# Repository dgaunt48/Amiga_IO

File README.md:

# MouseTest

RP2350 Program To Display Movement Counters,
Direction And Button Status Of An Amiga Mechanical Mouse.

# KeyboardTest

RP2350 Program To Decode And Display The Output From An A500 Keyboard.

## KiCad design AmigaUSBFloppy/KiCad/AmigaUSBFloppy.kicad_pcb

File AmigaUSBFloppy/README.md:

# Amiga USB Floppy

My Take On An Amiga GoTek Drive Using Parts I Had Lying Around.  Just A 2 Layer $2 PCB From JLC.

Firmware is at https://github.com/keirf/FlashFloppy

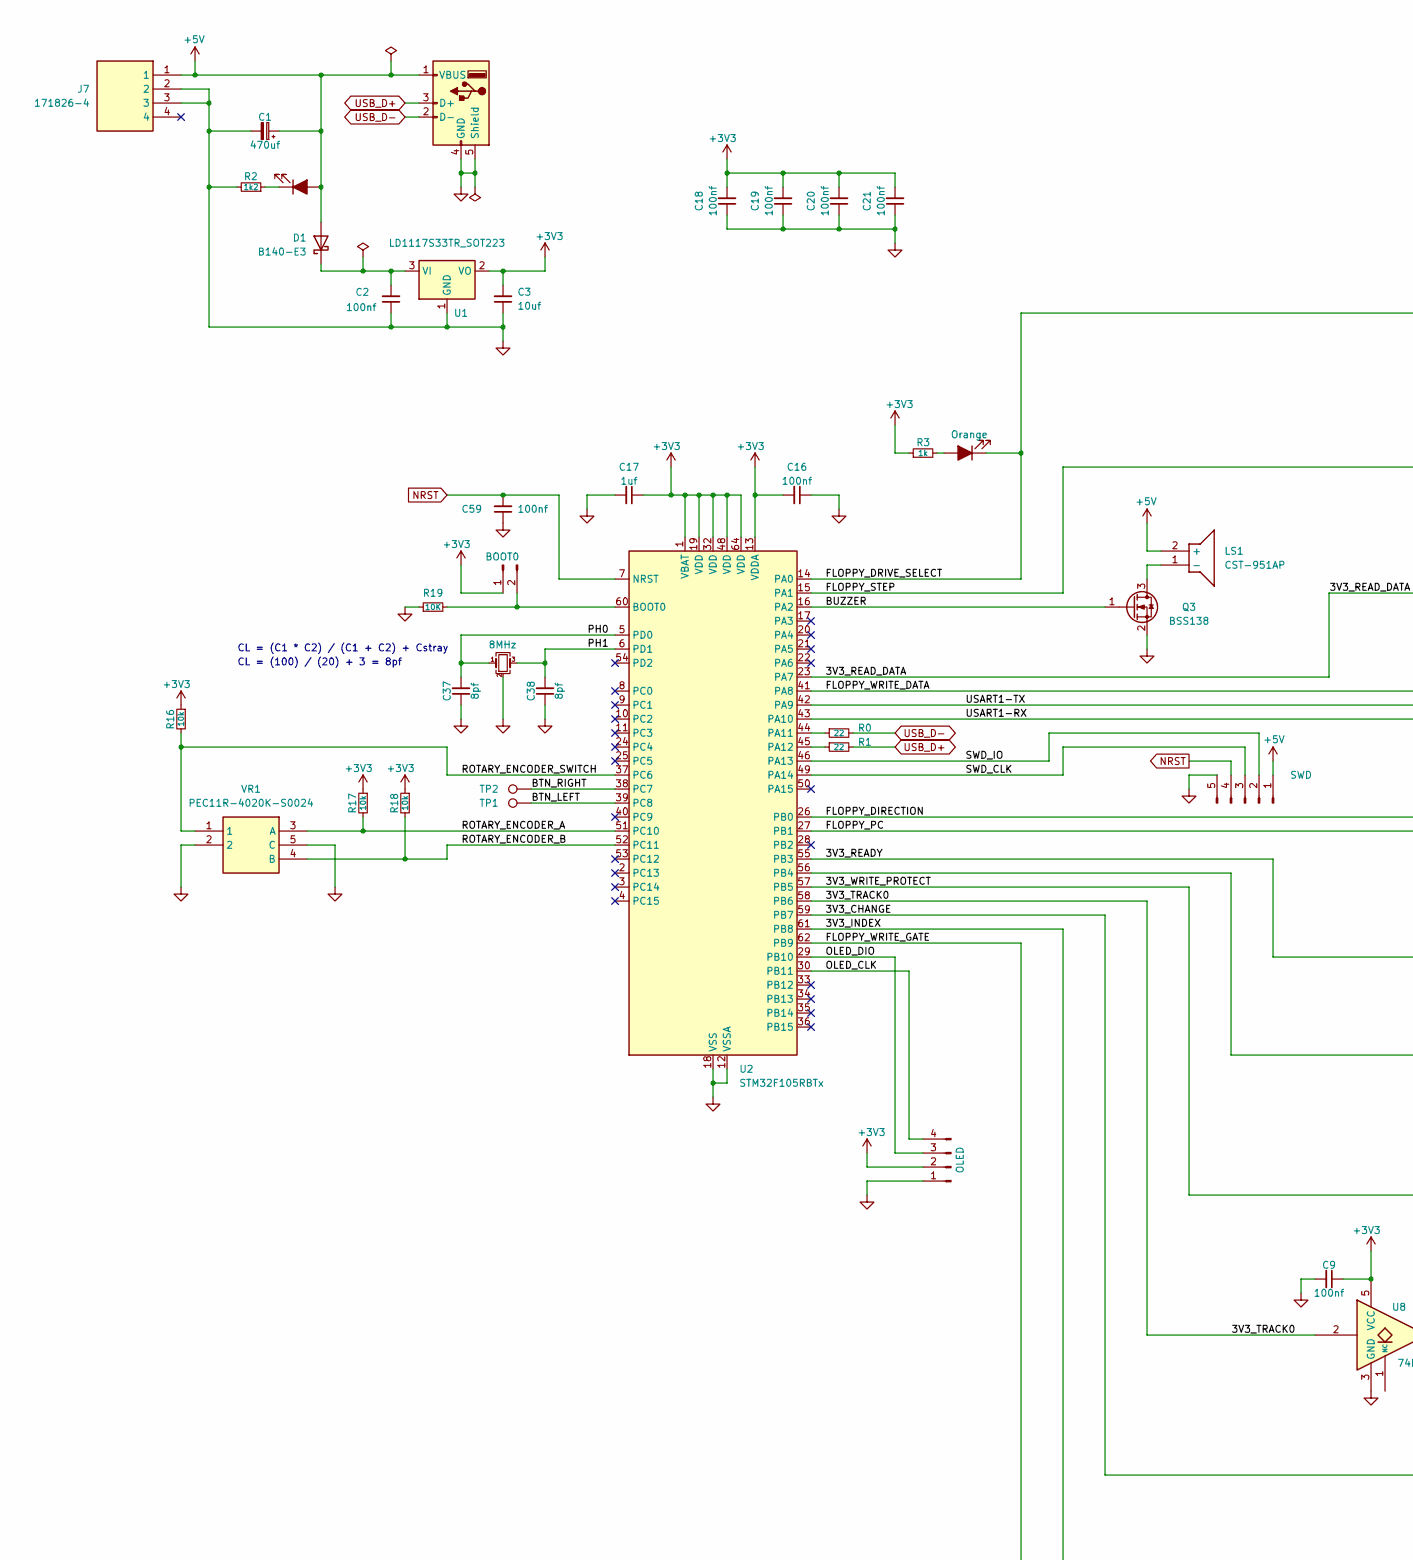
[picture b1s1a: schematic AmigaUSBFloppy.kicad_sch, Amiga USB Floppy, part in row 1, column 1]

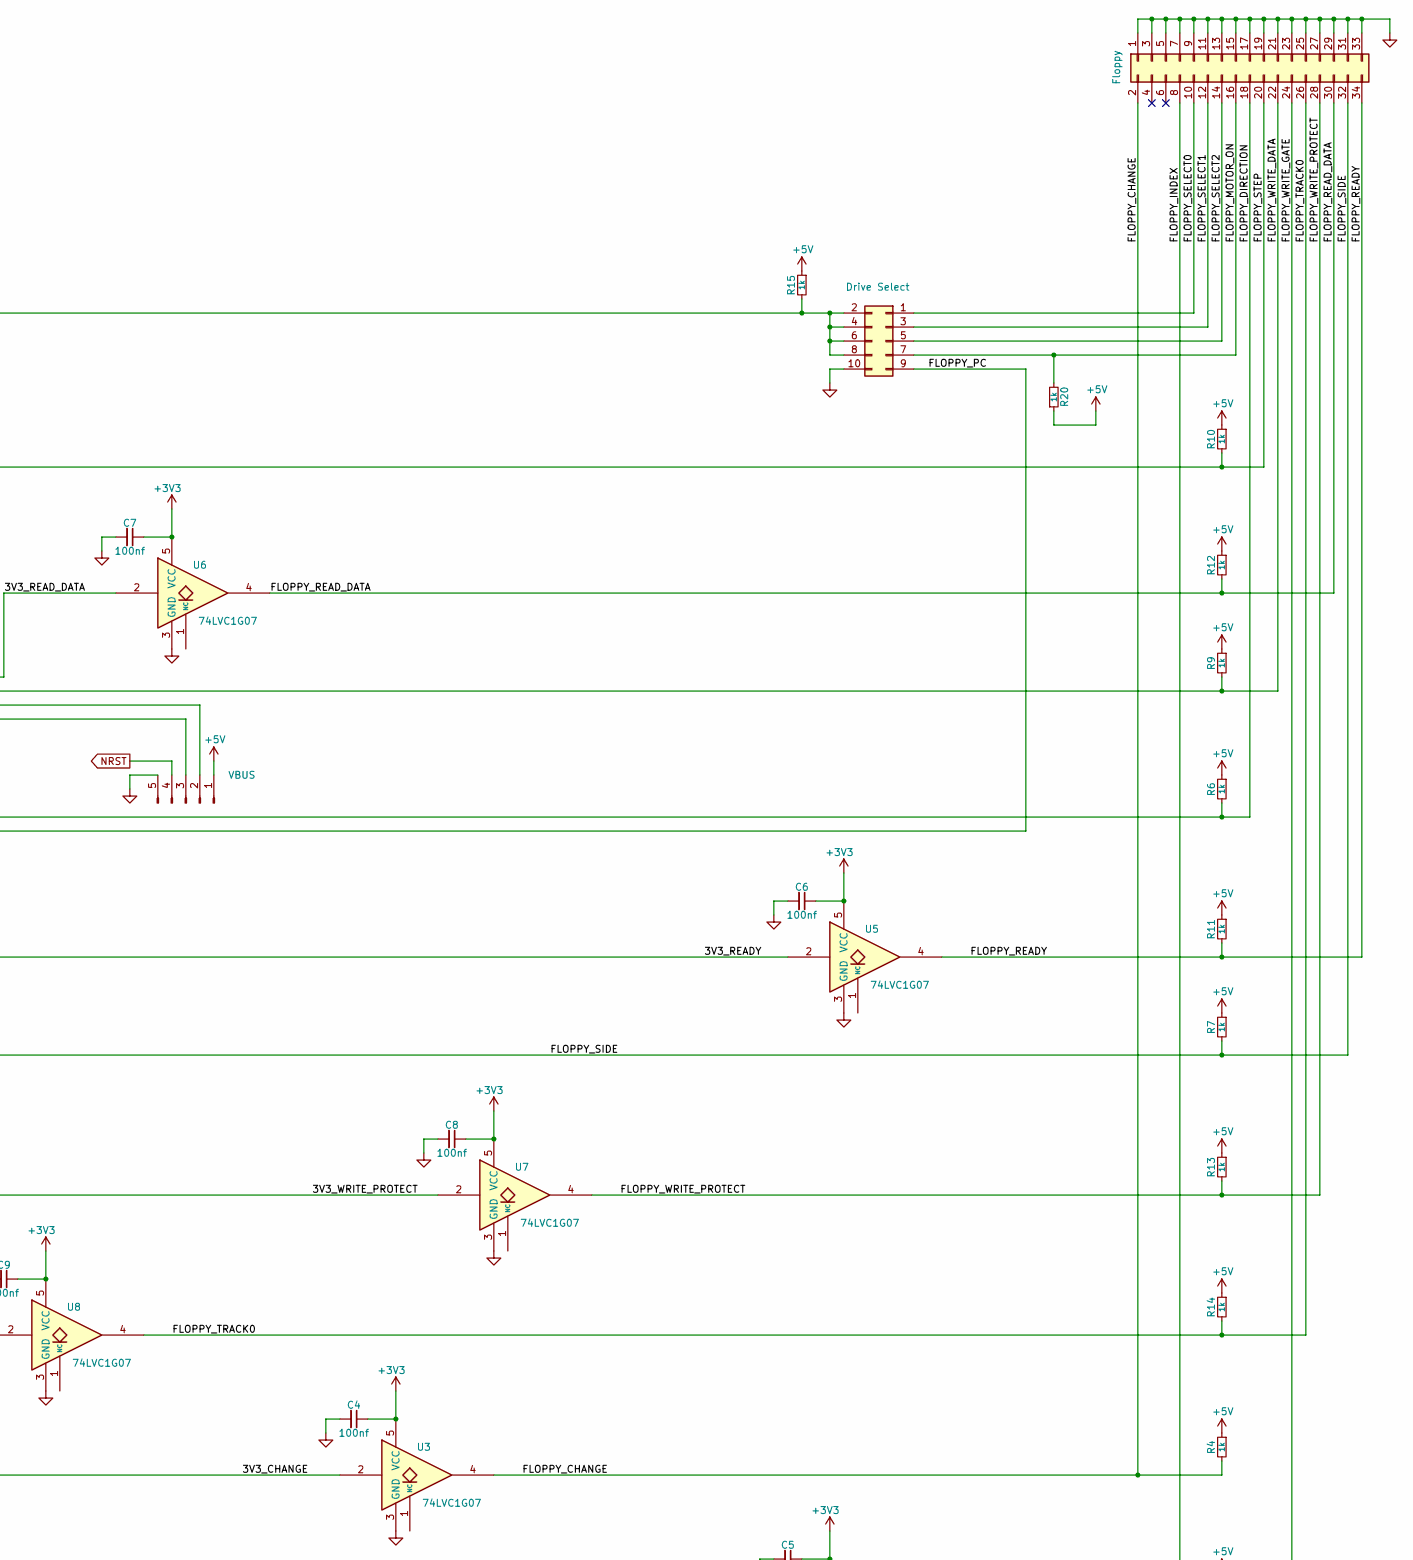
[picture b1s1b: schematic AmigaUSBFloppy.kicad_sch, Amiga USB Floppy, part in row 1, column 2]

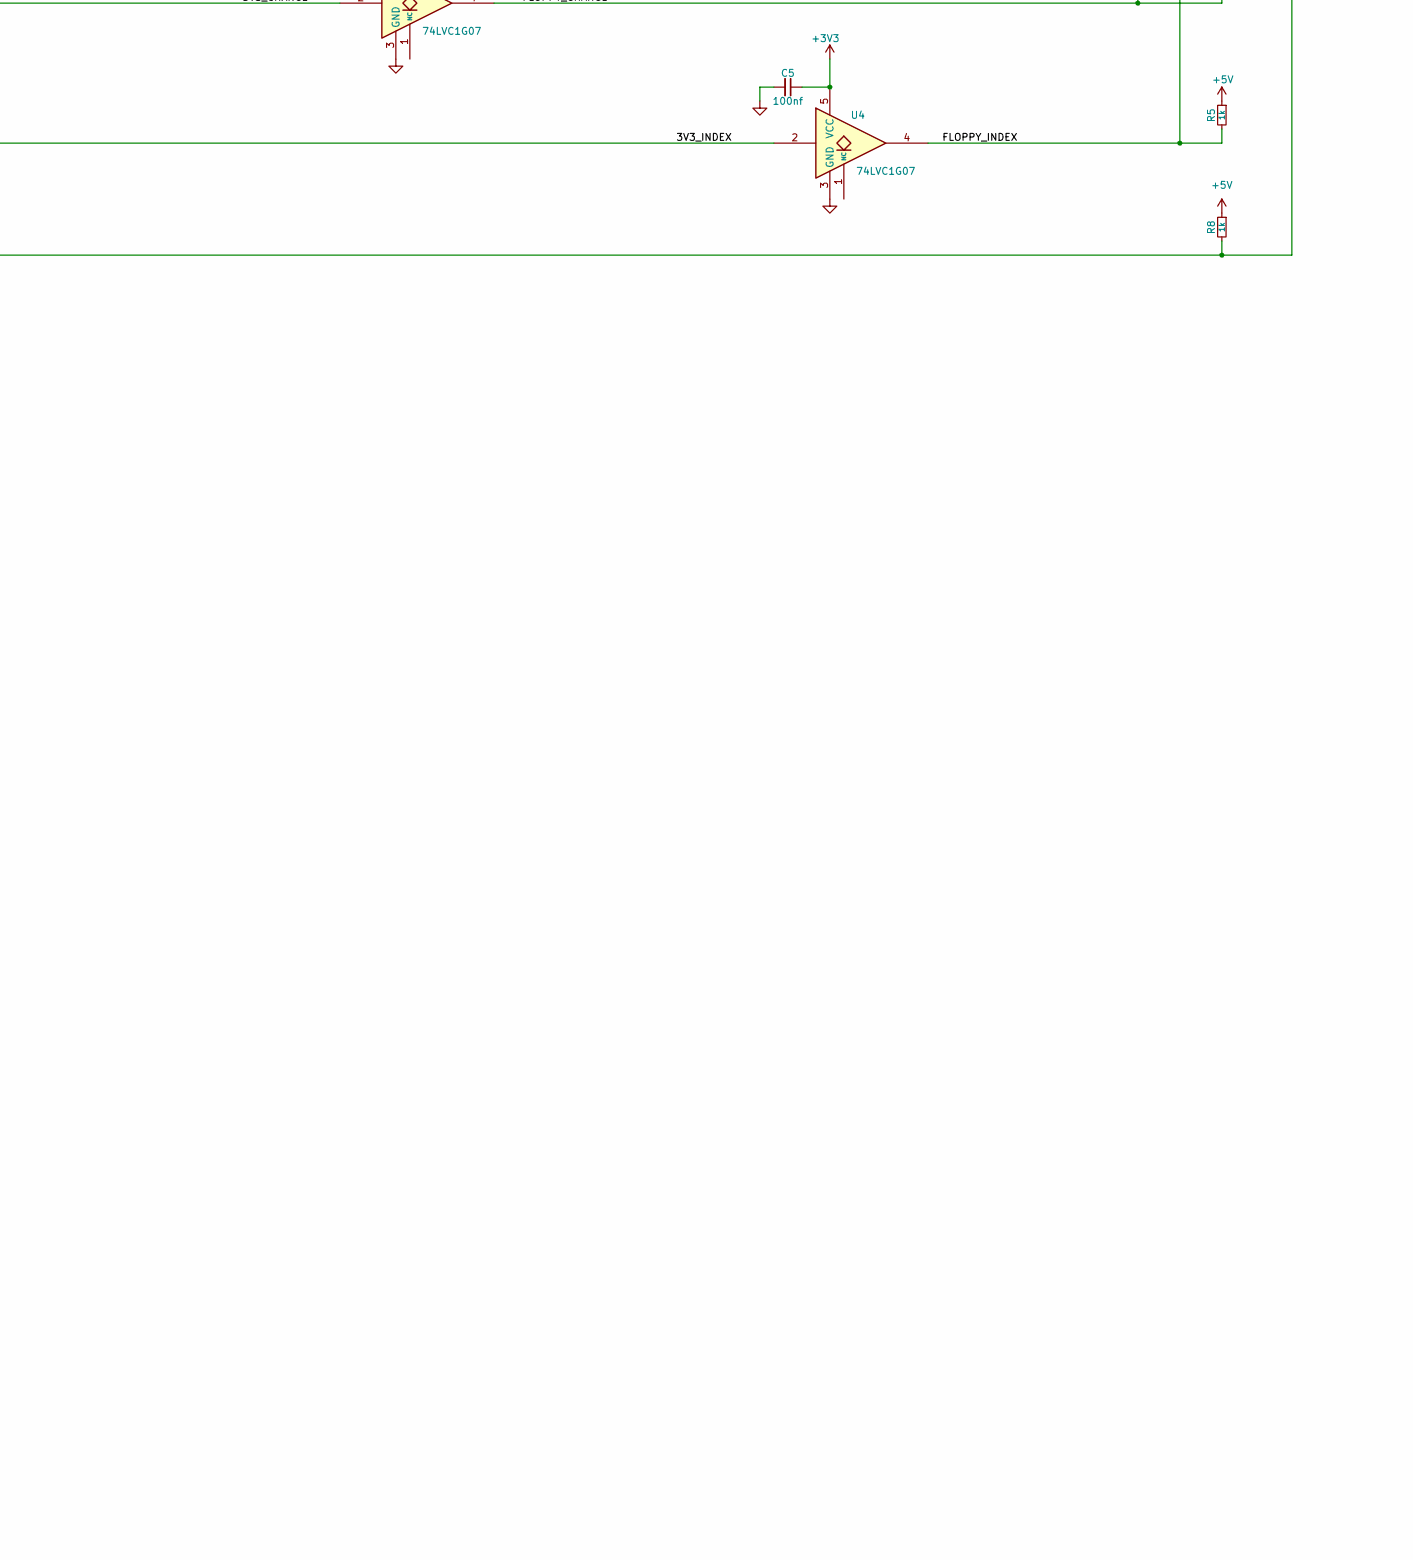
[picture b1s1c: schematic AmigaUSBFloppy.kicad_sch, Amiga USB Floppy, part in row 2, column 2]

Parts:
C1: 470uf; CP_Radial_D5.0mm_P2.50mm
C2, C4, C5, C6, C7, C8, C9, C16, C18, C19, C20, C21, C59: 100nf; C_0603_1608Metric
C3: 10uf; C_0805_2012Metric
C17: 1uf; C_0603_1608Metric
C37, C38: 8pf; C_0603_1608Metric
D1: B140-E3; D_SOD-123
H1, H2, H3, H4: MountingHole; MountingHole_2.5mm
J2: OLED; 128x64OLED
J3: Floppy; IDC-Header_2x17_P2.54mm_Vertical
J4: Drive Select; PinHeader_2x05_P2.54mm_Vertical
J5: BOOT0; PinHeader_1x02_P2.54mm_Vertical
J6: VBUS; PinHeader_1x05_P2.54mm_Vertical
J7: 171826-4; SHDRRA4W69P0X250_1X4_1000X1350X670P; Mouser Part Number 571-1718264
J11: SWD; PinHeader_1x05_P2.54mm_Vertical
J12: USB_A; USB_A_Molex_67643_Horizontal
LED1: POWER; LEDC2012X90N
LED2: Orange; LEDC2012X90N
LS1: CST-951AP; CST951AP; Mouser Part Number 490-CST-951AP
Q3: BSS138; SOT-23
R0, R1: 22; R_0603_1608Metric
R2: 1k2; R_0603_1608Metric
R3, R4, R5, R6, R7, R8, R9, R10, R11, R12, R13, R14, R15, R20: 1k; R_0603_1608Metric
R16, R17, R18: 10k; R_0603_1608Metric
R19: 10K; R_0603_1608Metric
TP1, TP2: TestPoint; TestPoint_Pad_1.0x1.0mm
U1: LD1117S33TR_SOT223; SOT-223-3_TabPin2; Voltage 3v3
U2: STM32F105RBTx; LQFP-64_10x10mm_P0.5mm
U3, U4, U5, U6, U7, U8: 74LVC1G07; SOT-353_SC-70-5
VR1: PEC11R-4020K-S0024; PEC11R-4XXXK-SXXXX; Mouser Part Number 652-PEC11R-4020K-S24
Y2: 8MHz; Crystal_SMD_SeikoEpson_FA238V-4Pin_3.2x2.5mm

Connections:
+3V3: C3.2, C4.1, C5.1, C6.1, C7.1, C8.1, C9.1, C16.2, C17.1, C18.2, C19.2, C20.2, C21.2, J2.2, J5.1, R3.1, R16.1, R17.1, R18.1, U1.2 (VO), U2.1 (VBAT), U2.13 (VDDA), U2.19 (VDD), U2.32 (VDD), U2.48 (VDD), U2.64 (VDD), U3.5 (VCC), U4.5 (VCC), U5.5 (VCC), U6.5 (VCC), U7.5 (VCC), U8.5 (VCC)
+5V: C1.1, D1.2 (A), J6.1, J7.1, J11.1, J12.1 (VBUS), LED1.2 (A), LS1.2 (+), R4.1, R5.1, R6.1, R7.1, R8.1, R9.1, R10.1, R11.1, R12.1, R13.1, R14.1, R15.1, R20.1
/3V3_CHANGE: U2.59 (PB7), U3.2
/3V3_INDEX: U2.61 (PB8), U4.2
/3V3_READY: U2.55 (PB3), U5.2
/3V3_READ_DATA: U2.23 (PA7), U6.2
/3V3_TRACK0: U2.58 (PB6), U8.2
/3V3_WRITE_PROTECT: U2.57 (PB5), U7.2
/BTN_LEFT: TP1.1, U2.39 (PC8)
/BTN_RIGHT: TP2.1, U2.38 (PC7)
/BUZZER: Q3.1 (G), U2.16 (PA2)
/FLOPPY_CHANGE: J3.2, R4.2, U3.4
/FLOPPY_DIRECTION: J3.18, R6.2, U2.26 (PB0)
/FLOPPY_DRIVE_SELECT: J4.2, J4.4, J4.6, J4.8, LED2.1 (K), R15.2, U2.14 (PA0)
/FLOPPY_INDEX: J3.8, R5.2, U4.4
/FLOPPY_MOTOR_ON: J3.16, J4.7, R20.2
/FLOPPY_PC: J4.9, U2.27 (PB1)
/FLOPPY_READY: J3.34, R11.2, U5.4
/FLOPPY_READ_DATA: J3.30, R12.2, U6.4
/FLOPPY_SELECT0: J3.10, J4.1
/FLOPPY_SELECT1: J3.12, J4.3
/FLOPPY_SELECT2: J3.14, J4.5
/FLOPPY_SIDE: J3.32, R7.2, U2.56 (PB4)
/FLOPPY_STEP: J3.20, R10.2, U2.15 (PA1)
/FLOPPY_TRACK0: J3.26, R14.2, U8.4
/FLOPPY_WRITE_DATA: J3.22, R9.2, U2.41 (PA8)
/FLOPPY_WRITE_GATE: J3.24, R8.2, U2.62 (PB9)
/FLOPPY_WRITE_PROTECT: J3.28, R13.2, U7.4
/OLED_CLK: J2.4, U2.30 (PB11)
/OLED_DIO: J2.3, U2.29 (PB10)
/PH0: C37.2, U2.5 (PD0), Y2.1
/PH1: C38.2, U2.6 (PD1), Y2.3
/ROTARY_ENCODER_A: R17.2, U2.51 (PC10), VR1.3 (A)
/ROTARY_ENCODER_B: R18.2, U2.52 (PC11), VR1.4 (B)
/ROTARY_ENCODER_SWITCH: R16.2, U2.37 (PC6), VR1.1
/SWD_CLK: J11.3, U2.49 (PA14)
/SWD_IO: J11.2, U2.46 (PA13)
/USART1-RX: J6.3, U2.43 (PA10)
/USART1-TX: J6.2, U2.42 (PA9)
GND: C1.2, C2.1, C3.1, C4.2, C5.2, C6.2, C7.2, C8.2, C9.2, C16.1, C17.2, C18.1, C19.1, C20.1, C21.1, C37.1, C38.1, C59.1, J2.1, J3.1, J3.3, J3.5, J3.7, J3.9, J3.11, J3.13, J3.15, J3.17, J3.19, J3.21, J3.23, J3.25, J3.27, J3.29, J3.31, J3.33, J4.10, J6.5, J7.2, J7.3, J11.5, J12.4 (GND), J12.5 (Shield), Q3.2 (S), R2.2, R19.1, U1.1 (GND), U2.12 (VSSA), U2.18 (VSS), U2.31 (VSS), U2.47 (VSS), U2.63 (VSS), U3.3 (GND), U4.3 (GND), U5.3 (GND), U6.3 (GND), U7.3 (GND), U8.3 (GND), VR1.2, VR1.5 (C), Y2.2 (G), Y2.4 (G)
NRST: C59.2, J6.4, J11.4, U2.7 (NRST)
unnamed: C2.2, D1.1 (K), U1.3 (VI)
unnamed: J5.2, R19.2, U2.60 (BOOT0)
unnamed: LED1.1 (K), R2.1
unnamed: LED2.2 (A), R3.2
unnamed: LS1.1 (-), Q3.3 (D)
unnamed: R0.1, U2.44 (PA11)
unnamed: R1.1, U2.45 (PA12)
USB_D+: J12.3 (D+), R1.2
USB_D-: J12.2 (D-), R0.2

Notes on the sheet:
CL = (100) / (20) + 3 = 8pf
CL = (C1 * C2) / (C1 + C2) + Cstray

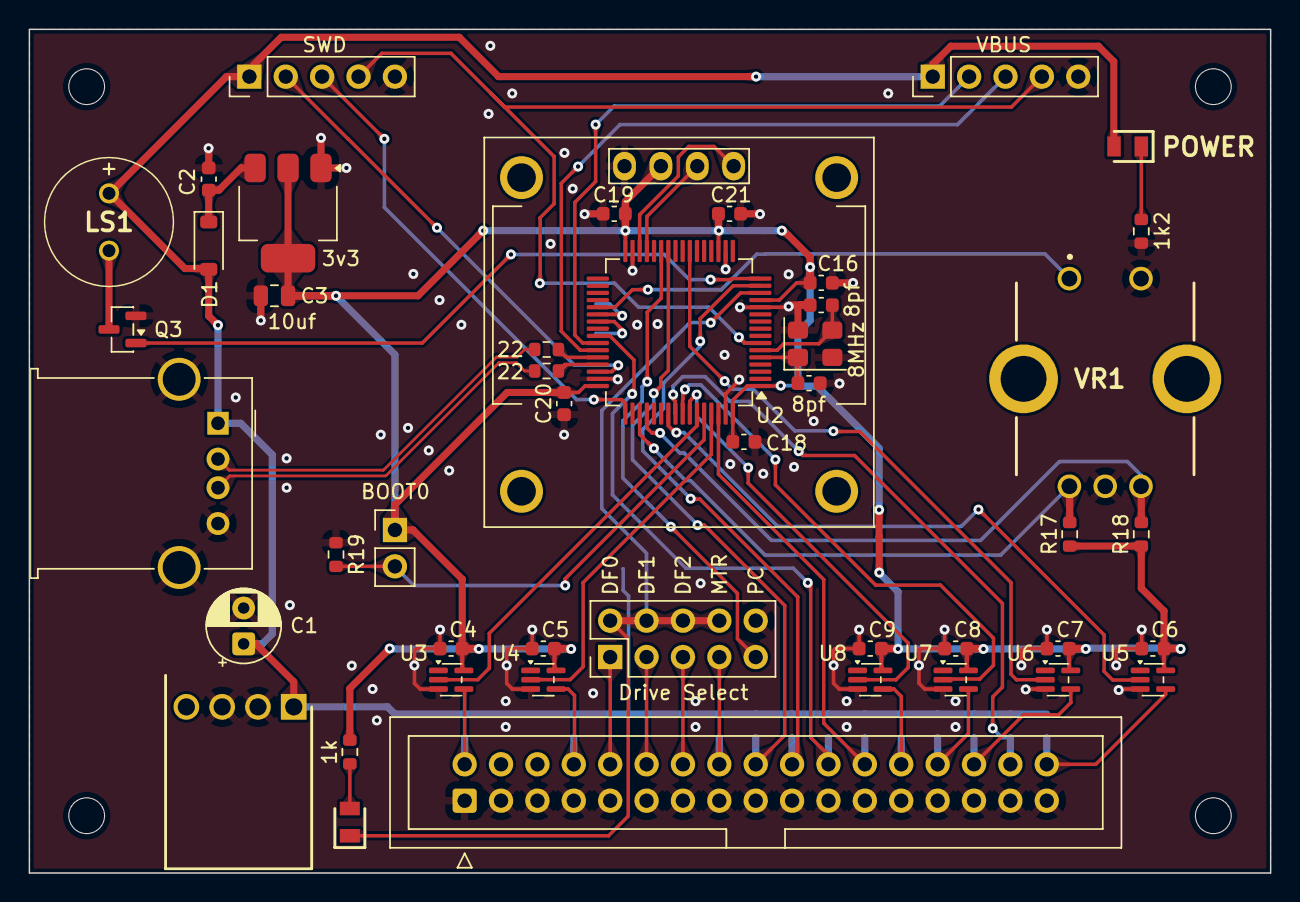
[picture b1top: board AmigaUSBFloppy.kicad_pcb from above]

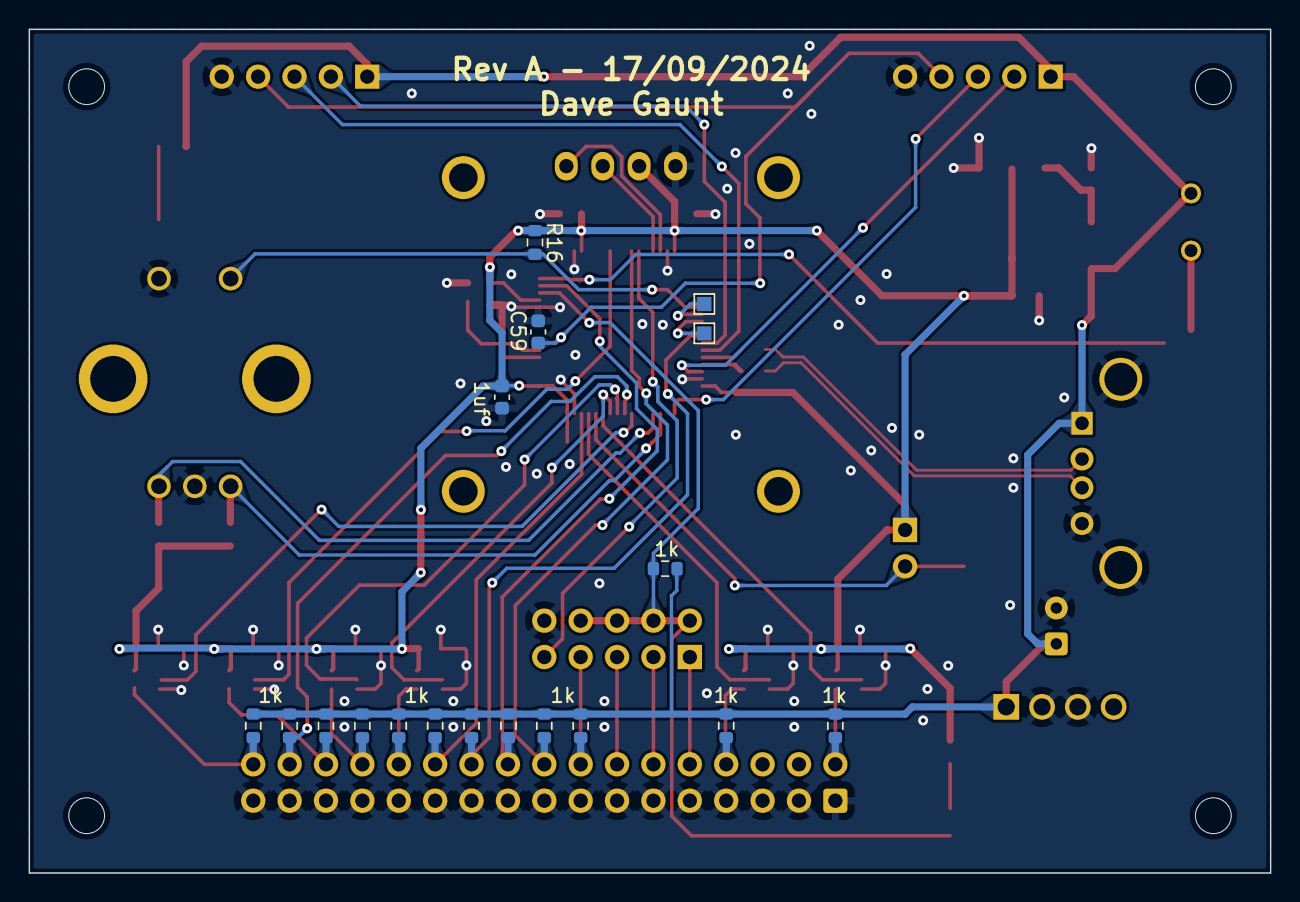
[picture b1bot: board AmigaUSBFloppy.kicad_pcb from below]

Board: 2 copper layers, 86.7 x 58.9 mm, 68 parts (18 on the bottom side), 50 nets.

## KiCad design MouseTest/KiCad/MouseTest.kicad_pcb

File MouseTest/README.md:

# Amiga Mouse Test

Simple RP2350 Program To Display The Movement Counters,
Direction And Button Status Of An Amiga Mechanical Mouse.

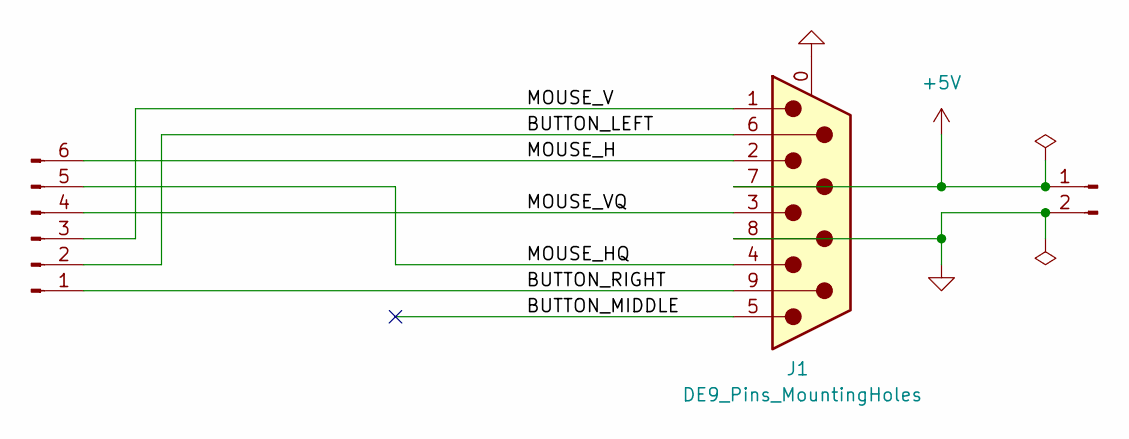
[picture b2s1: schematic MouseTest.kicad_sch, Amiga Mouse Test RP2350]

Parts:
J1: DE9_Pins_MountingHoles; DSUB-9_Pins_Horizontal_P2.77x2.84mm_EdgePinOffset4.94mm_Hou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
J2: Conn_01x02_Pin; PinHeader_1x02_P2.54mm_Vertical
J3: Conn_01x02_Pin; PinHeader_1x06_P2.54mm_Vertical

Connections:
+5V: J1.7, J2.1
/BUTTON_LEFT: J1.6, J3.2
/BUTTON_MIDDLE: J1.5
/BUTTON_RIGHT: J1.9, J3.1
/MOUSE_H: J1.2, J3.6
/MOUSE_HQ: J1.4, J3.5
/MOUSE_V: J1.1, J3.3
/MOUSE_VQ: J1.3, J3.4
GND: J1.0 (PAD), J1.8, J2.2

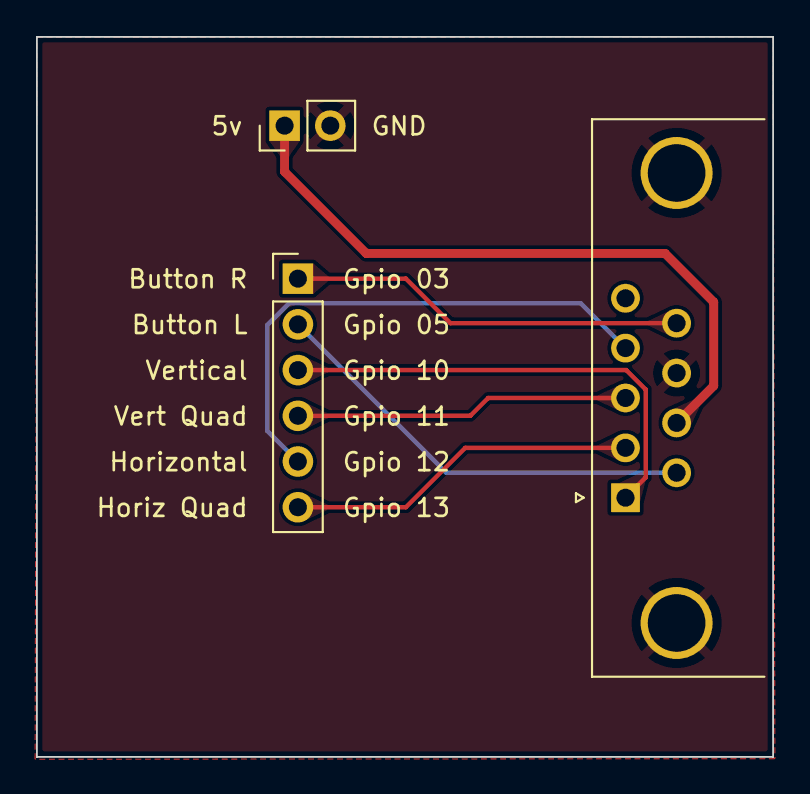
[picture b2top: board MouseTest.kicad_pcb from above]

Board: 2 copper layers, 40.9 x 40.0 mm, 3 parts (0 on the bottom side), 8 nets.

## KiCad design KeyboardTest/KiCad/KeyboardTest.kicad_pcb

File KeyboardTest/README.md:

# Amiga 500 Keyboard Test

RP2350 Program To Decode And Display The Key Presses From An Amiga 500 Keyboard.

Connections To The RP2350

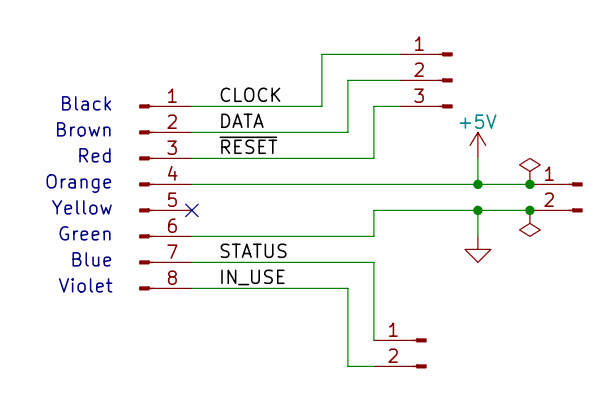
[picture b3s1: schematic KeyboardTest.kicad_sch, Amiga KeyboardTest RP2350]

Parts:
J1: Conn_01x02_Pin; PinHeader_1x03_P2.54mm_Vertical
J3: A500 Keyboard; PinHeader_1x08_P2.54mm_Vertical
J4, J5: Conn_01x02_Pin; PinHeader_1x02_P2.54mm_Vertical

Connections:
+5V: J3.4, J4.1
/CLOCK: J1.1, J3.1
/DATA: J1.2, J3.2
/IN_USE: J3.8, J5.2
/RESET: J1.3, J3.3
/STATUS: J3.7, J5.1
GND: J3.6, J4.2

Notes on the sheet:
Black
Red
Yellow
Green
Blue
Violet
Brown
Orange

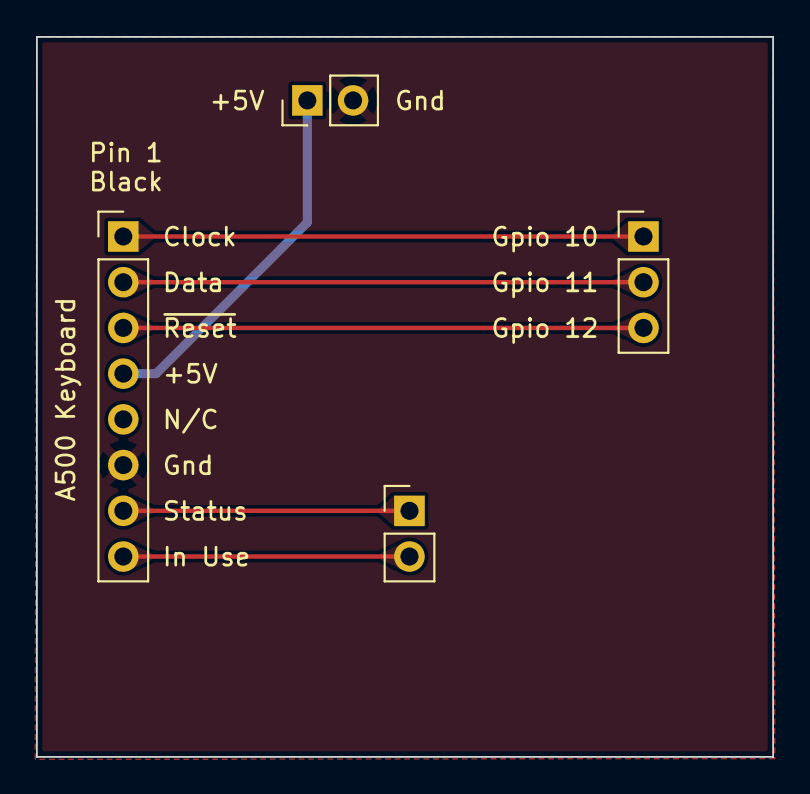
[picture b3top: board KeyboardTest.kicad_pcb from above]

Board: 2 copper layers, 40.9 x 40.0 mm, 4 parts (0 on the bottom side), 7 nets.

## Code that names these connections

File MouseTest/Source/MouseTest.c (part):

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#define TERMINAL_CHARS_WIDE		(VGA_RESOLUTION_X >> 3)
#define TERMINAL_CHARS_HIGH		(VGA_RESOLUTION_Y >> 3)

enum vga_pins {PIN_RED = 0, PIN_GREEN, PIN_BLUE, PIN_BUTTON_RIGHT, PIN_BUTTON_LEFT = 5, PIN_HSYNC = 8, PIN_VSYNC, PIN_MOUSE_V = 10, PIN_MOUSE_VQ, PIN_MOUSE_HQ, PIN_MOUSE_H};

enum rgbColours {RGB_BLACK, RGB_RED, RGB_GREEN, RGB_YELLOW, RGB_BLUE, RGB_MAGENTA, RGB_CYAN, RGB_WHITE};

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	save_and_disable_interrupts();

	u32 uLow32Pins = gpioc_lo_in_get();
	u32 uCurrentH = (uLow32Pins >> PIN_MOUSE_H) & 1;
	u32 uCurrentV = (uLow32Pins >> PIN_MOUSE_V) & 1;

 	while(true)
 	{
		uLow32Pins = gpioc_lo_in_get();

		if (uCurrentH != ((uLow32Pins >> PIN_MOUSE_H) & 1))
		{
			uCurrentH = (uLow32Pins >> PIN_MOUSE_H) & 1;

			if(uCurrentH)
			{
				delay_40ns();
				uLow32Pins = gpioc_lo_in_get();
				s_uDirectionH = (uLow32Pins >> PIN_MOUSE_HQ) & 1;
				++s_uCountH;
			}
		}

		if (uCurrentV != ((uLow32Pins >> PIN_MOUSE_V) & 1))
		{
			uCurrentV = (uLow32Pins >> PIN_MOUSE_V) & 1;

			if(uCurrentV)
			{
				delay_40ns();
				uLow32Pins = gpioc_lo_in_get();
				s_uDirectionV = (uLow32Pins >> PIN_MOUSE_VQ) & 1;
				++s_uCountV;
			}
		}
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{
	stdio_init_all();

	gpio_init(PIN_BUTTON_LEFT);
    gpio_set_dir(PIN_BUTTON_LEFT, GPIO_IN);
	gpio_set_pulls(PIN_BUTTON_LEFT, true, false);

	gpio_init(PIN_BUTTON_RIGHT);
    gpio_set_dir(PIN_BUTTON_RIGHT, GPIO_IN);
	gpio_set_pulls(PIN_BUTTON_RIGHT, true, false);

	gpio_init(PIN_MOUSE_V);
    gpio_set_dir(PIN_MOUSE_V, GPIO_IN);

	gpio_init(PIN_MOUSE_VQ);
    gpio_set_dir(PIN_MOUSE_VQ, GPIO_IN);

	gpio_init(PIN_MOUSE_H);
    gpio_set_dir(PIN_MOUSE_H, GPIO_IN);

	gpio_init(PIN_MOUSE_HQ);
    gpio_set_dir(PIN_MOUSE_HQ, GPIO_IN);

	multicore_launch_core1(function_core1);

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	{
		const u32 uLow32Pins = gpioc_lo_in_get();

		sprintf(szTempString, "Left Button %d      Right Button %d", ~(uLow32Pins >> PIN_BUTTON_LEFT) & 1, ~(uLow32Pins >> PIN_BUTTON_RIGHT) & 1);
		DrawString(20, 30, szTempString, RGB_YELLOW);

		sprintf(szTempString, "Last  Vertical  Move Was %s  Count = %d", (s_uDirectionV & 1) ? "Up   " : "Down ", s_uCountV);
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
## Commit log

2026-02-15 - Added RP2350 Amiga Mechanical Mouse Test.
2026-02-15 - Added The A500 Keyboard Test.
2026-02-15 - Added USB Floppy Drive KiCad Project.
2026-02-15 - Added my misc junk folder to ignore.
